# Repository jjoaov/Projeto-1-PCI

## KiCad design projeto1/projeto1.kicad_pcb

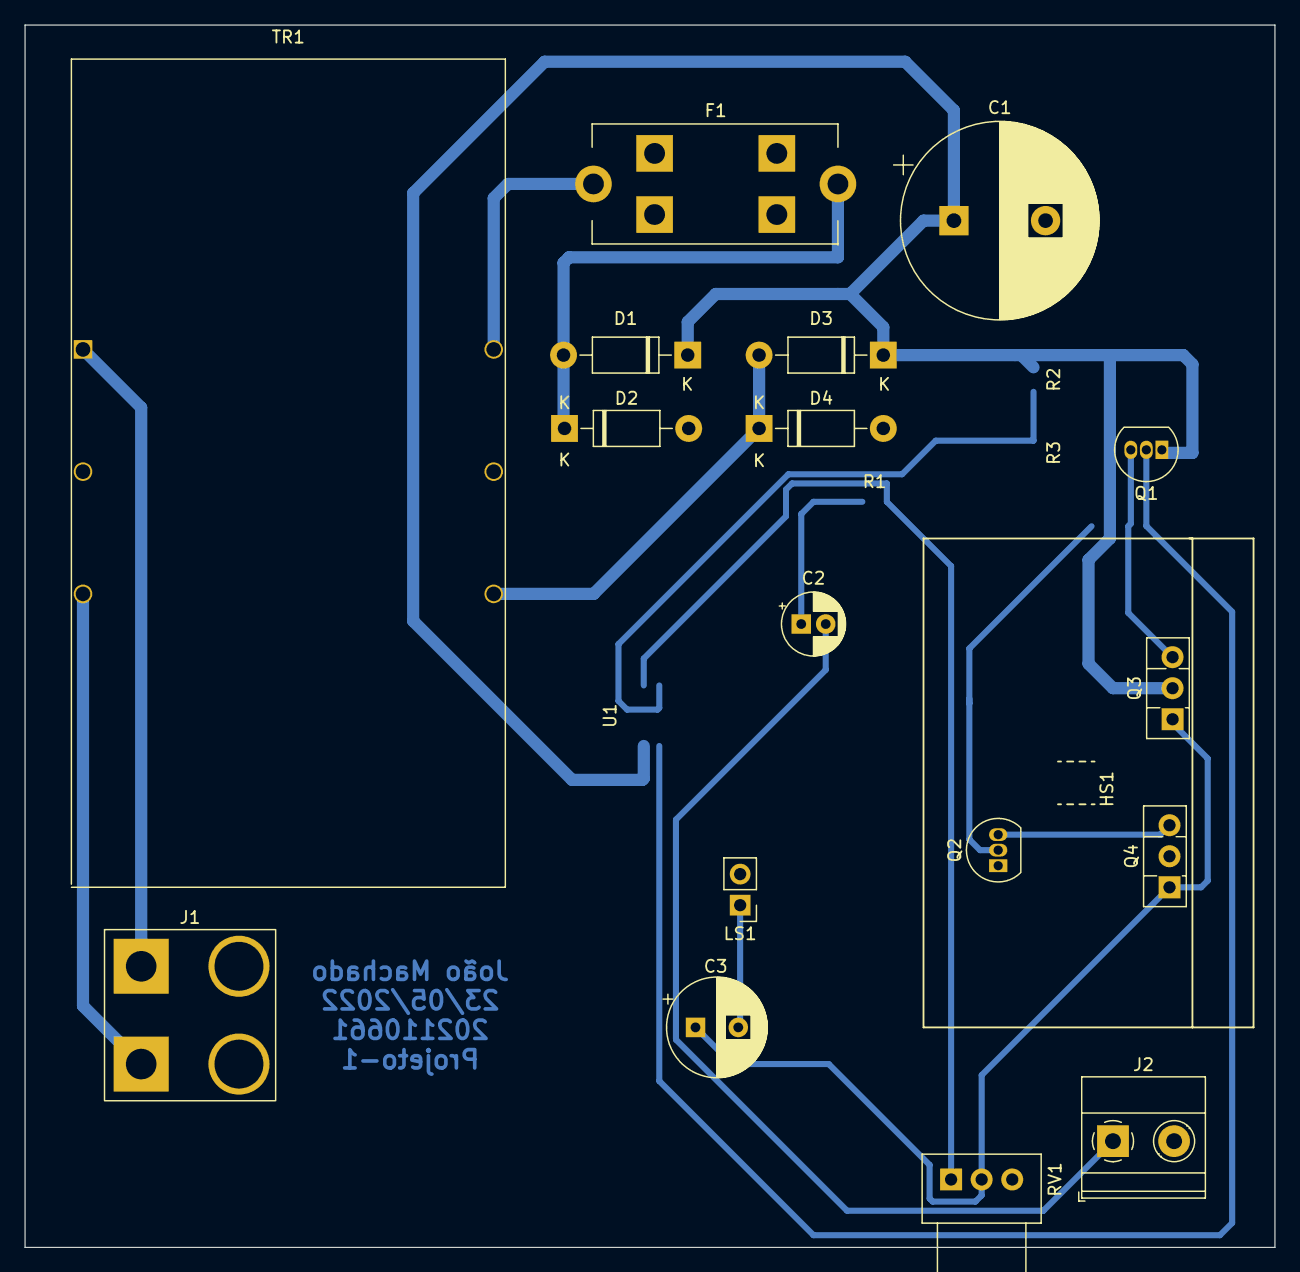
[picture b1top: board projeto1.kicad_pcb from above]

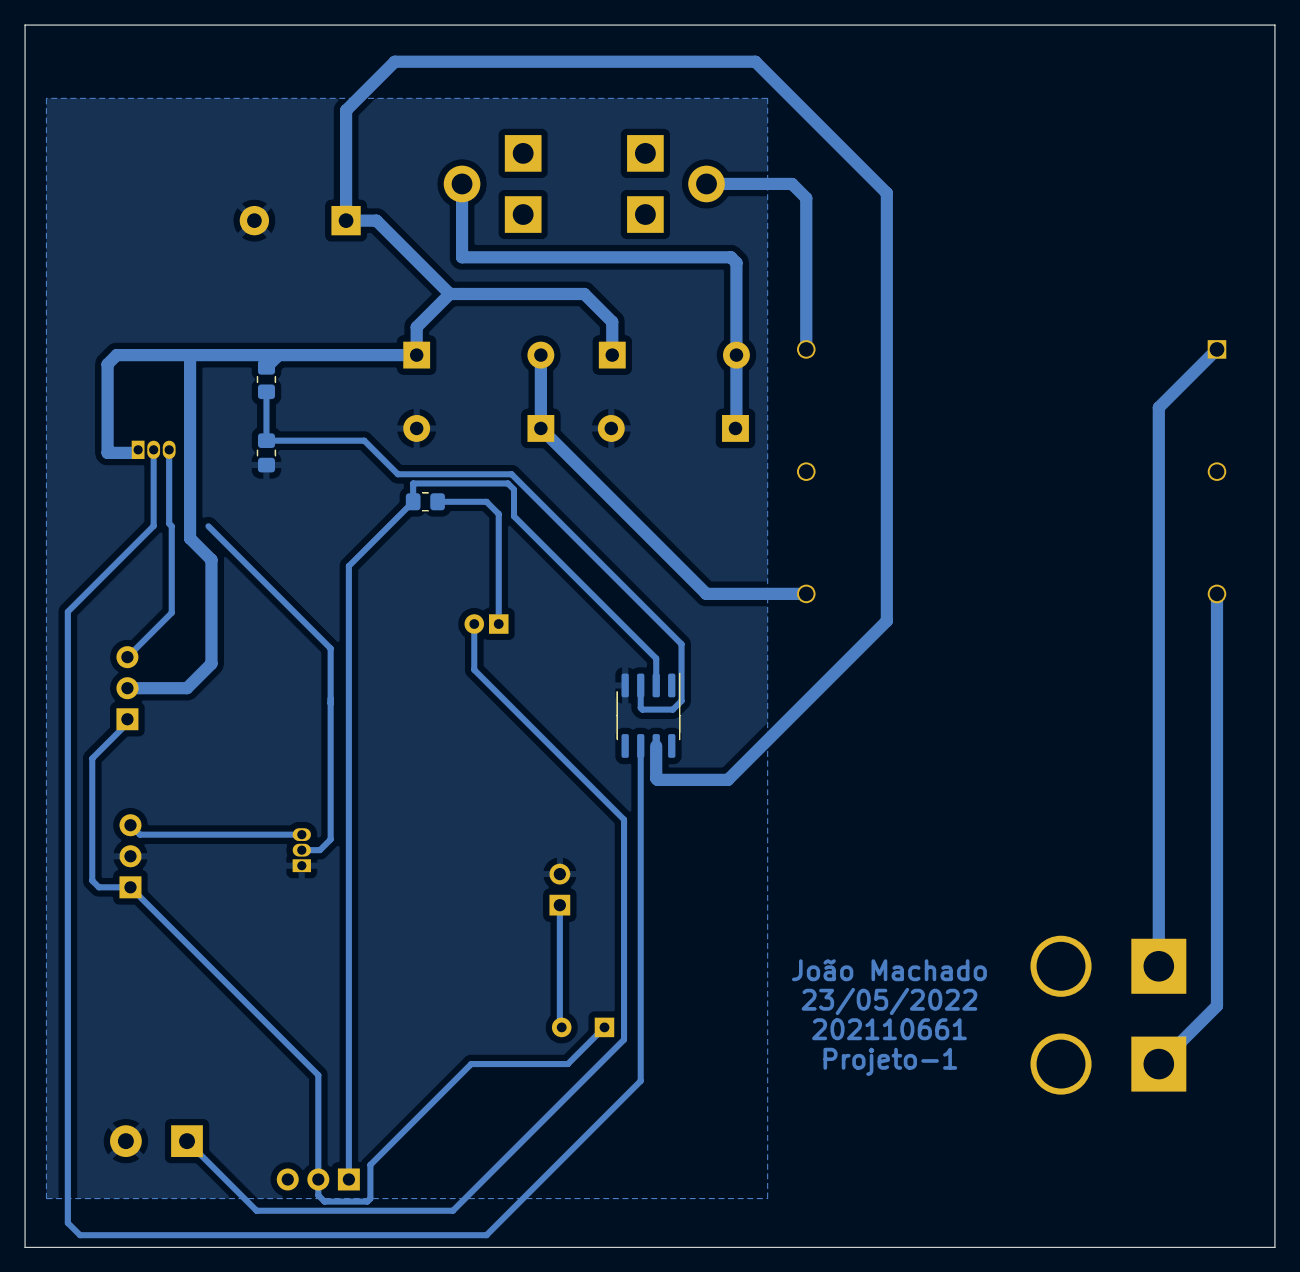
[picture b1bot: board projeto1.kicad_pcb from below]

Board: 2 copper layers, 102.2 x 100.0 mm, 22 parts (4 on the bottom side), 16 nets.

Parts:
C1: 2.2m; CP_Radial_D16.0mm_P7.50mm
C2: 2.2u; CP_Radial_D5.0mm_P2.00mm
C3: 1m; CP_Radial_D8.0mm_P3.50mm
D1, D2, D3, D4: 1N4007; D_DO-41_SOD81_P10.16mm_Horizontal
F1: Fuse_; Fuseholder_
HS1: Heatsink; Heatsink_
J1: Entrada_Alimentação; Input_
J2: Conn_01x02_Male; TerminalBlock_Phoenix_MKDS-1,5-2_1x02_P5.00mm_Horizontal
LS1: Speaker; PinHeader_1x02_P2.54mm_Vertical
Q1: BC548; TO-92_Inline
Q2: BC556; TO-92_Inline
Q3: BD135; TO-126-3_Vertical
Q4: BD136; TO-126-3_Vertical
R1: 1k; R_0805_2012Metric_Pad1.20x1.40mm_HandSolder
R2, R3: 10k; R_0805_2012Metric_Pad1.20x1.40mm_HandSolder
RV1: 200k; Potentiometer_Alps_RK09Y11_Single_Horizontal
TR1: Transformer_
U1: TL071; SOIC-8_3.9x4.9mm_P1.27mm

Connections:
/INPUT_PWR: C1.1, D1.1 (K), D3.1 (K), Q1.1 (C), Q3.2 (C), R2.2, U1.7 (V+)
GND: C1.2, D2.2 (A), D4.2 (A), J2.2, LS1.2, Q2.1 (C), Q4.2 (C), R3.1, U1.4 (V-)
unnamed: C2.1, R1.2
unnamed: C2.2, J2.1
unnamed: C3.1, Q3.1 (E), Q4.1 (E), RV1.2
unnamed: C3.2, LS1.1
unnamed: D1.2 (A), D2.1 (K), F1.2
unnamed: D3.2 (A), D4.1 (K), TR1.4
unnamed: F1.1, TR1.6
unnamed: J1.1, TR1.1
unnamed: J1.2, TR1.3
unnamed: Q1.2 (B), Q2.2 (B), U1.6
unnamed: Q1.3 (E), Q3.3 (B)
unnamed: Q2.3 (E), Q4.3 (B)
unnamed: R1.1, RV1.1, U1.2 (-)
unnamed: R2.1, R3.2, U1.3 (+)

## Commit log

2022-06-14 rev-1
